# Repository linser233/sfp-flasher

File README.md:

# SFP_FLASHER

SFP/QSFP Flash Tool

QSFP-DD Pinout
| Pin | Symbol   | Description                          |
|-----|----------|--------------------------------------|
| 1   | GND      | Ground                               |
| 2   | Tx2n     | Transmitter Inverted Data Input      |
| 3   | Tx2p     | Transmitter Non-Inverted Data Input  |
| 4   | GND      | Ground                               |
| 5   | Tx4n     | Transmitter Inverted Data Input      |
| 6   | Tx4p     | Transmitter Non-Inverted Data Input  |
| 7   | GND      | Ground                               |
| 8   | ModSelL  | Module Select                        |
| 9   | ResetL   | Module Reset                         |
| 10  | Vcc Rx   | +3.3V Power Supply Receiver          |
| 11  | SCL      | 2-wire Serial Interface Clock        |
| 12  | SDA      | 2-wire Serial Interface Data         |
| 13  | GND      | GND                                  |
| 14  | Rx3p     | Receiver Non-Inverted Data Output    |
| 15  | Rx3n     | Receiver Inverted Data Output        |
| 16  | GND      | Ground                               |
| 17  | Rx1p     | Receiver Non-Inverted Data Output    |
| 18  | Rx1n     | Receiver Inverted Data Output        |
| 19  | GND      | Ground                               |
| 20  | GND      | Ground                               |
| 21  | Rx2n     | Receiver Inverted Data Output        |
| 22  | Rx2p     | Receiver Non-Inverted Data Output    |
| 23  | GND      | Grounds                              |
| 24  | Rx4n     | Receiver Inverted Data Output        |
| 25  | Rx4p     | Receiver Non-Inverted Data Output    |
| 26  | GND      | Ground                               |
| 27  | ModPrsL  | Module Present                       |
| 28  | IntL     | Interrupt                            |
| 29  | Vcc Tx   | +3.3V Power Supply Transmitter       |
| 30  | Vcc1     | +3.3V Power Supply                   |
| 31  | LPMode   | Low Power Mode                       |
| 32  | GND      | Ground                               |
| 33  | Tx3p     | Transmitter Non-Inverted Data Input  |
| 34  | Tx3n     | Transmitter Inverted Data Input      |
| 35  | GND      | Ground                               |
| 36  | Tx1p     | Transmitter Non-Inverted Data Input  |
| 37  | Tx1n     | Transmitter Inverted Data Input      |
| 38  | GND      | Ground                               |
| 39  | GND      | Ground                               |
| 40  | Tx6n     | Transmitter Inverted Data Input      |
| 41  | Tx6p     | Transmitter Non-Inverted Data Input  |
| 42  | GND      | Ground                               |
| 43  | Tx8n     | Transmitter Inverted Data Input      |
| 44  | Tx8p     | Transmitter Non-Inverted Data Input  |
| 45  | GND      | Ground                               |
| 46  | Reserved | For future use                       |
| 47  | VS1      | Module Vendor Specific 1             |
| 48  | VccRx1   | 3.3V Power Supply                    |
| 49  | VS2      | Module Vendor Specific 2             |
| 50  | VS3      | Module Vendor Specific 3             |
| 51  | GND      | Ground                               |
| 52  | Rx7p     | Receiver Non-Inverted Data Output    |
| 53  | Rx7n     | Receiver Inverted Data Output        |
| 54  | GND      | Ground                               |
| 55  | Rx5p     | Receiver Non-Inverted Data Output    |
| 56  | Rx5n     | Receiver Inverted Data Output        |
| 57  | GND      | Ground                               |
| 58  | GND      | Ground                               |
| 59  | Rx6n     | Receiver Inverted Data Output        |
| 60  | Rx6p     | Receiver Non-Inverted Data Output    |
| 61  | GND      | Ground                               |
| 62  | Rx8n     | Receiver Inverted Data Output        |
| 63  | Rx8p     | Receiver Non-Inverted Data Output    |
| 64  | GND      | Ground                               |
| 65  | NC       | No Connect                           |
| 66  | Reserved | For future use                       |
| 67  | VccTx1   | 3.3V Power Supply                    |
| 68  | Vcc2     | 3.3V Power Supply                    |
| 69  | Reserved | For Future Use                       |
| 70  | GND      | Ground                               |
| 71  | Tx7p     | Transmitter Non-Inverted Data Input  |
| 72  | Tx7n     | Transmitter Inverted Data Input      |
| 73  | GND      | Ground                               |
| 74  | Tx5p     | Transmitter Non-Inverted Data Input  |
| 75  | Tx5n     | Transmitter Inverted Data Input      |
| 76  | GND      | Ground                               |

Control Signals
| Name    | Function             | Description                                                                                                                                                                                                 |
|---------|----------------------|-------------------------------------------------------------------------------------------------------------------------------------------------------------------------------------------------------------|
| ModPrsL | Output, asserted low | Pull-up by host when no transceiver/cable is present. Connected to ground inside the transceiver. Hence, asserted low when a transceiver/cable is plugged in.                                               |
| ModSelL | Input, asserted Low  | Module Select input pin, terminated high in the module. Only when held low by the host, the module responds to 2-wire serial communication commands. Enables multiple modules to share a single 2-wire bus. |
| ResetL  | Input, asserted Low  | Reset input pin, pulled high in the module. A low level on the ResetL pin for longer than the minimum length initiates a module reset. When de-asserted the transceiver starts initialization.              |
| LPMode  | Input, asserted high | Low Power Mode input, pulled up inside the module. Hardware control signal for forcing the transceiver into low-power state. Can be overwritten by low-power mode command.                                  |
| ePPS    | Input                | Not implemented                                                                                                                                                                                             |
| IntL    | Output, asserted low | Interrupt Low is an open-collector output, terminated high in the host system. A “Low” indicates a possible module operational fault or a status critical to the host system, e.g. temperature alarm.       |

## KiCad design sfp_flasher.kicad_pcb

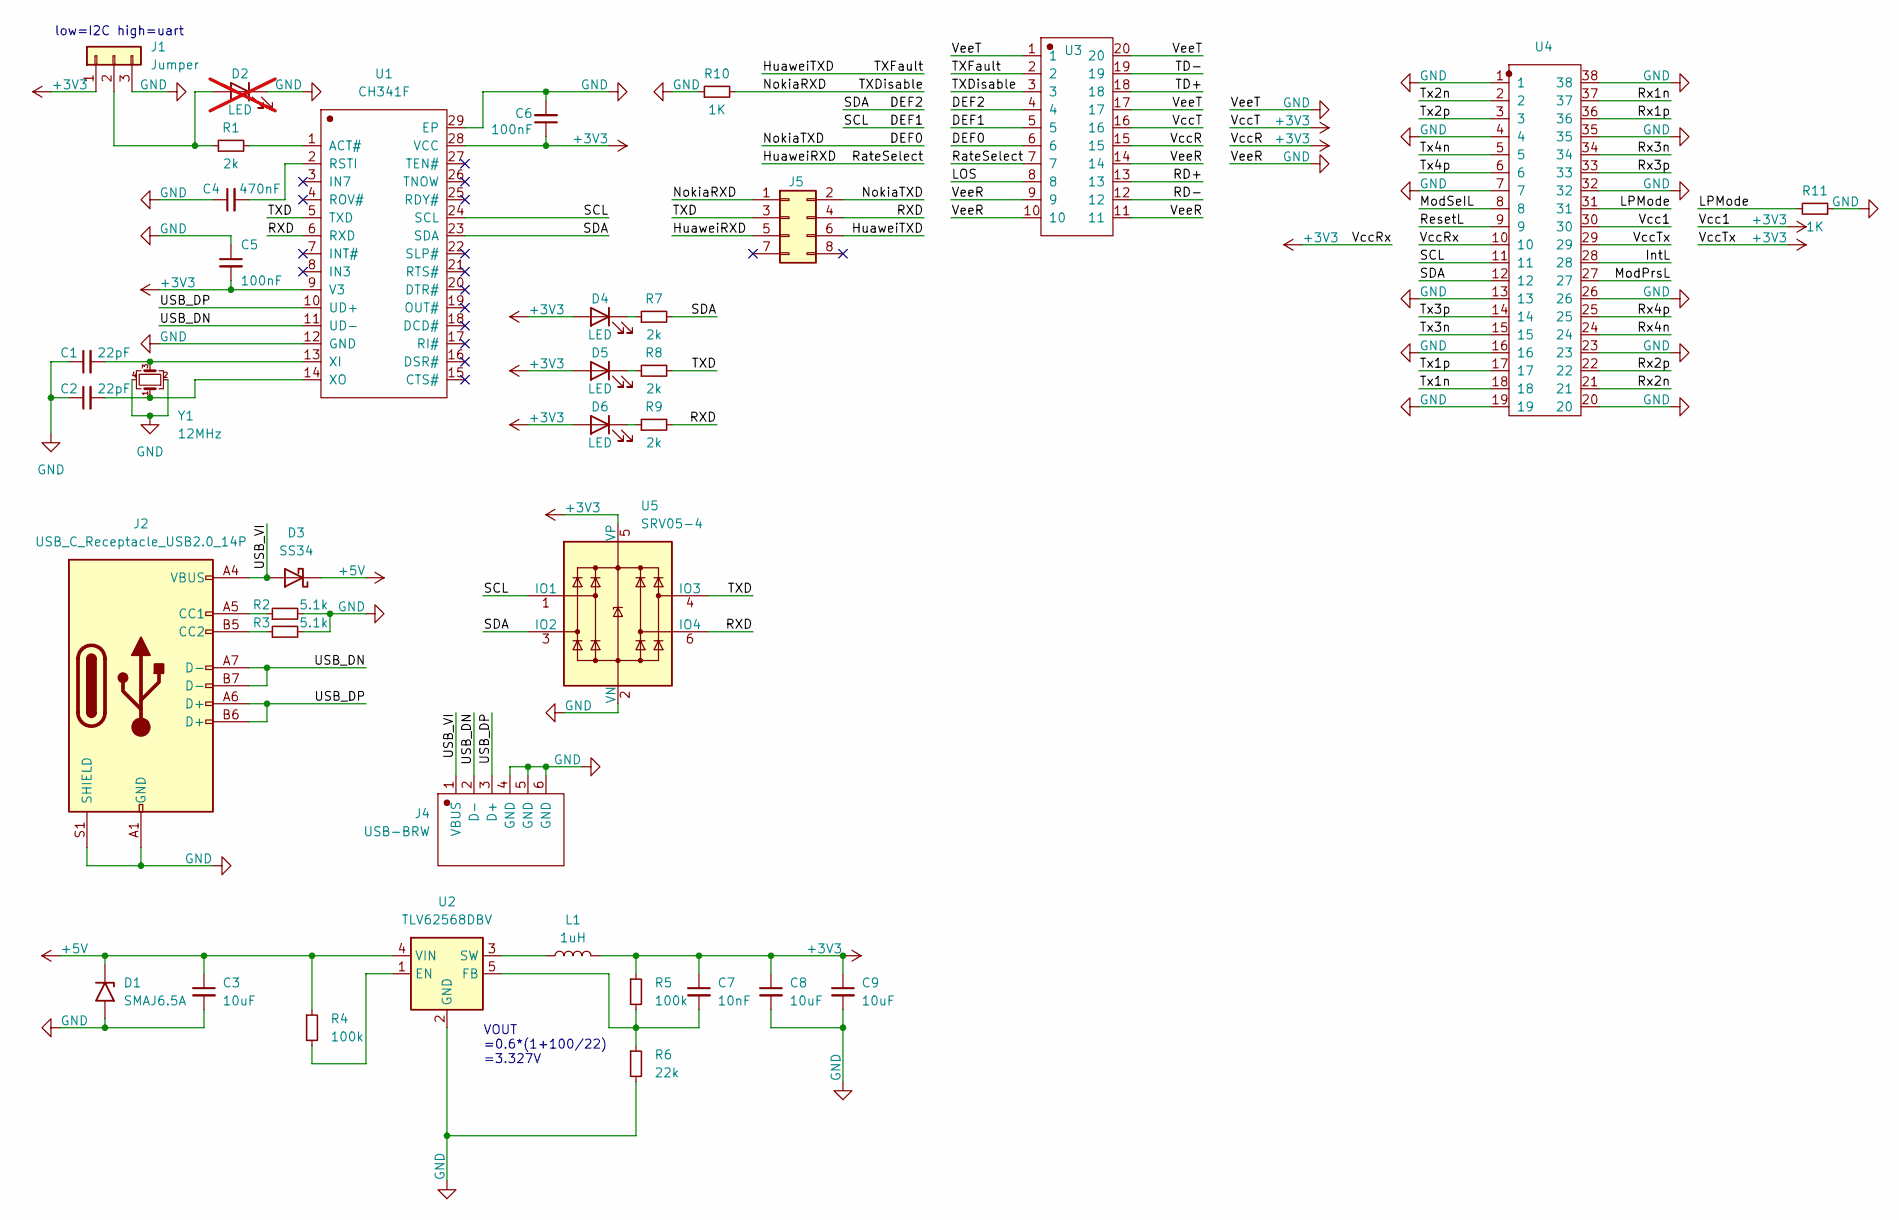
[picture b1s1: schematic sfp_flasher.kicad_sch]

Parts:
C1, C2: 22pF; C_0603_1608Metric; LCSC C1555
C3, C8, C9: 10uF; C_0805_2012Metric
C4: 470nF; C_0603_1608Metric
C5, C6: 100nF; C_0603_1608Metric; LCSC C1525
C7: 10nF; C_0603_1608Metric
D1: SMAJ6.5A; D_SMA
D2: LED; LED_0603_1608Metric; not fitted
D3: SS34; D_SMA
D4: LED; LED_D3.0mm
D5, D6: LED; LED_0603_1608Metric
J1: Jumper; PinHeader_1x03_P2.54mm_Vertical
J2: USB_C_Receptacle_USB2.0_14P; USB_C_Receptacle_Palconn_UTC16-G
J4: USB-BRW; USB_B_OST_USB-B1HSxx_Horizontal
J5: uart; PinHeader_2x04_P2.54mm_Vertical
L1: 1uH; L_1008_2520Metric
R1, R7, R8, R9: 2k; R_0603_1608Metric; LCSC C11702
R2, R3: 5.1k; R_0603_1608Metric; LCSC C11702
R4, R5: 100k; R_0603_1608Metric; LCSC C11702
R6: 22k; R_0603_1608Metric; LCSC C11702
R10, R11: 1K; R_0603_1608Metric; LCSC C11702
U1: CH341F; QFN-28_L4.0-W4.0-P0.40-BL-EP
U2: TLV62568DBV; SOT-23-5
U3: XDSFP-020-0852; CONN-SMD_20P-P0.80-H_M42F-08P-020-P002G
U4: UMAX952L0301; CONN-SMD_UMAX952L0301
U5: SRV05-4; SOT-23-6
Y1: 12MHz; Crystal_SMD_SeikoEpson_TSX3225-4Pin_3.2x2.5mm; LCSC C9002

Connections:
+3V3: C5.2, C6.1, C7.1, C8.1, C9.1, D4.2 (A), D5.2 (A), D6.2 (A), J1.1, L1.2, R5.1, U1.9 (V3), U1.28 (VCC), U3.15, U3.16, U4.10, U4.29, U4.30, U5.5 (VP)
+5V: C3.1, D1.1 (A1), D3.1 (K), R4.1, U2.4 (VIN)
/DEF0: J5.2, U3.6
/DEF1: U1.24 (SCL), U3.5, U4.11, U5.1 (IO1)
/DEF2: R7.2, U1.23 (SDA), U3.4, U4.12, U5.3 (IO2)
/HuaweiRXD: J5.5, U3.7
/HuaweiTXD: J5.6, U3.2
/IntL: U4.28
/LOS: U3.8
/LPMode: R11.2, U4.31
/ModPrsL: U4.27
/ModSeIL: U4.8
/NokiaRXD: J5.1, R10.2, U3.3
/RD+: U3.13
/RD-: U3.12
/RXD: J5.4, R9.2, U1.6 (RXD), U5.6 (IO4)
/ResetL: U4.9
/Rx1n: U4.37
/Rx1p: U4.36
/Rx2n: U4.21
/Rx2p: U4.22
/Rx3n: U4.34
/Rx3p: U4.33
/Rx4n: U4.24
/Rx4p: U4.25
/TD+: U3.18
/TD-: U3.19
/TXD: J5.3, R8.2, U1.5 (TXD), U5.4 (IO3)
/Tx1n: U4.18
/Tx1p: U4.17
/Tx2n: U4.2
/Tx2p: U4.3
/Tx3n: U4.15
/Tx3p: U4.14
/Tx4n: U4.5
/Tx4p: U4.6
/USB_DN: J2.A7 (D-), J2.B7 (D-), J4.2 (D-), U1.11 (UD-)
/USB_DP: J2.A6 (D+), J2.B6 (D+), J4.3 (D+), U1.10 (UD+)
/USB_VI: D3.2 (A), J2.A4 (VBUS), J2.A9 (VBUS), J2.B4 (VBUS), J2.B9 (VBUS), J4.1 (VBUS)
GND: C1.1, C2.1, C3.2, C4.1, C5.1, C6.2, C8.2, C9.2, D1.2 (A2), D2.1 (K), J1.3, J2.A1 (GND), J2.A12 (GND), J2.B1 (GND), J2.B12 (GND), J2.S1 (SHIELD), J4.4 (GND), J4.5 (GND), J4.6 (GND), R2.2, R3.2, R6.2, R10.1, R11.1, U1.12 (GND), U1.29 (EP), U2.2 (GND), U3.1, U3.9, U3.10, U3.11, U3.14, U3.17, U3.20, U4.1, U4.4, U4.7, U4.13, U4.16, U4.19, U4.20, U4.23, U4.26, U4.32, U4.35, U4.38, U5.2 (VN), Y1.2, Y1.4
unnamed: D2.2 (A), J1.2, R1.1
unnamed: D4.1 (K), R7.1
unnamed: D5.1 (K), R8.1
unnamed: D6.1 (K), R9.1
unnamed: J2.A5 (CC1), R2.1
unnamed: J2.B5 (CC2), R3.1
unnamed: R1.2, U1.1 (ACT#)
unnamed: C4.2, U1.2 (RSTI)
unnamed: C1.2, U1.13 (XI), Y1.3
unnamed: C2.2, U1.14 (XO), Y1.1
unnamed: R4.2, U2.1 (EN)
unnamed: C7.2, R5.2, R6.1, U2.5 (FB)
unnamed: L1.1, U2.3 (SW)

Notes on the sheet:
VOUT =0.6*(1+100/22) =3.327V
low=I2C high=uart

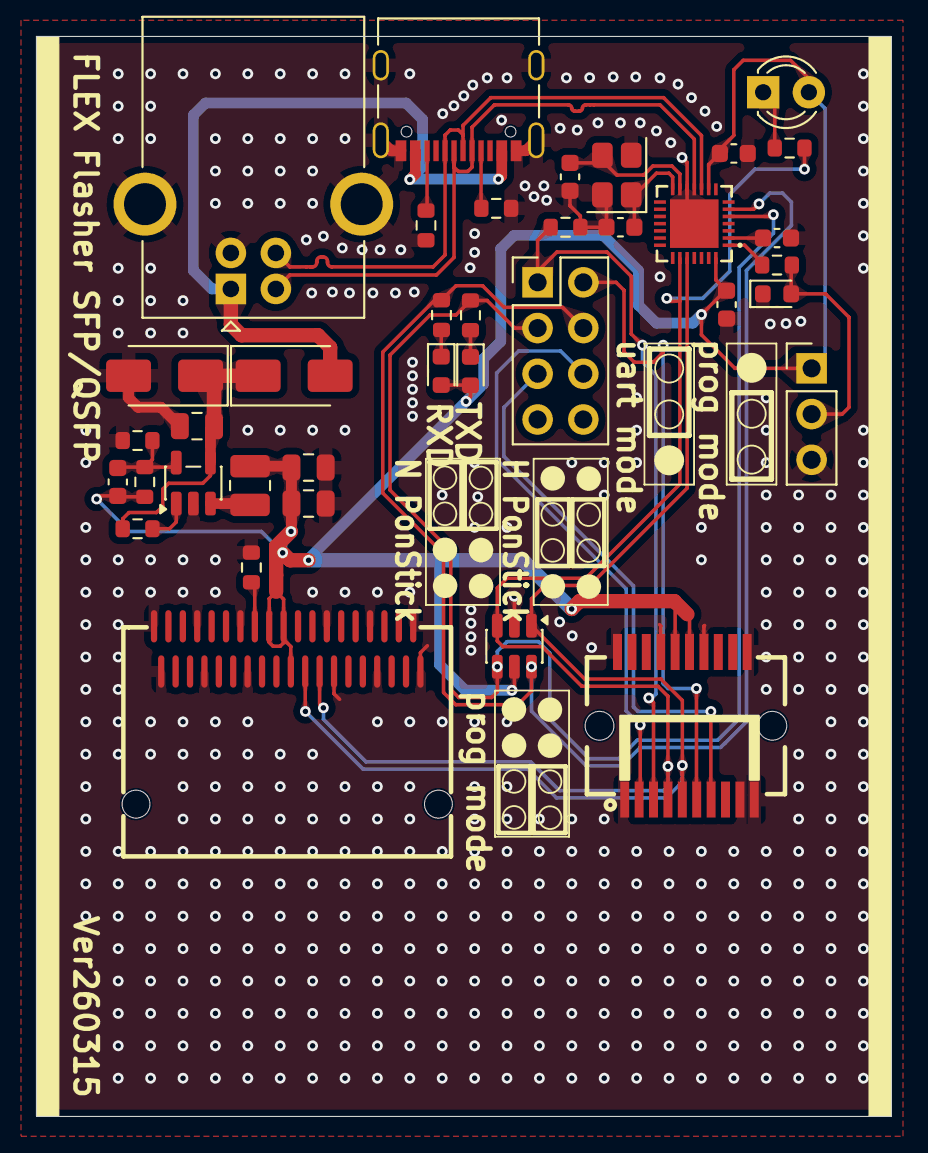
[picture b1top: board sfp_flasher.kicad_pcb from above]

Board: 2 copper layers, 47.5 x 60.0 mm, 37 parts (0 on the bottom side), 28 nets.

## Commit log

2026-06-11 Create LISENCE
